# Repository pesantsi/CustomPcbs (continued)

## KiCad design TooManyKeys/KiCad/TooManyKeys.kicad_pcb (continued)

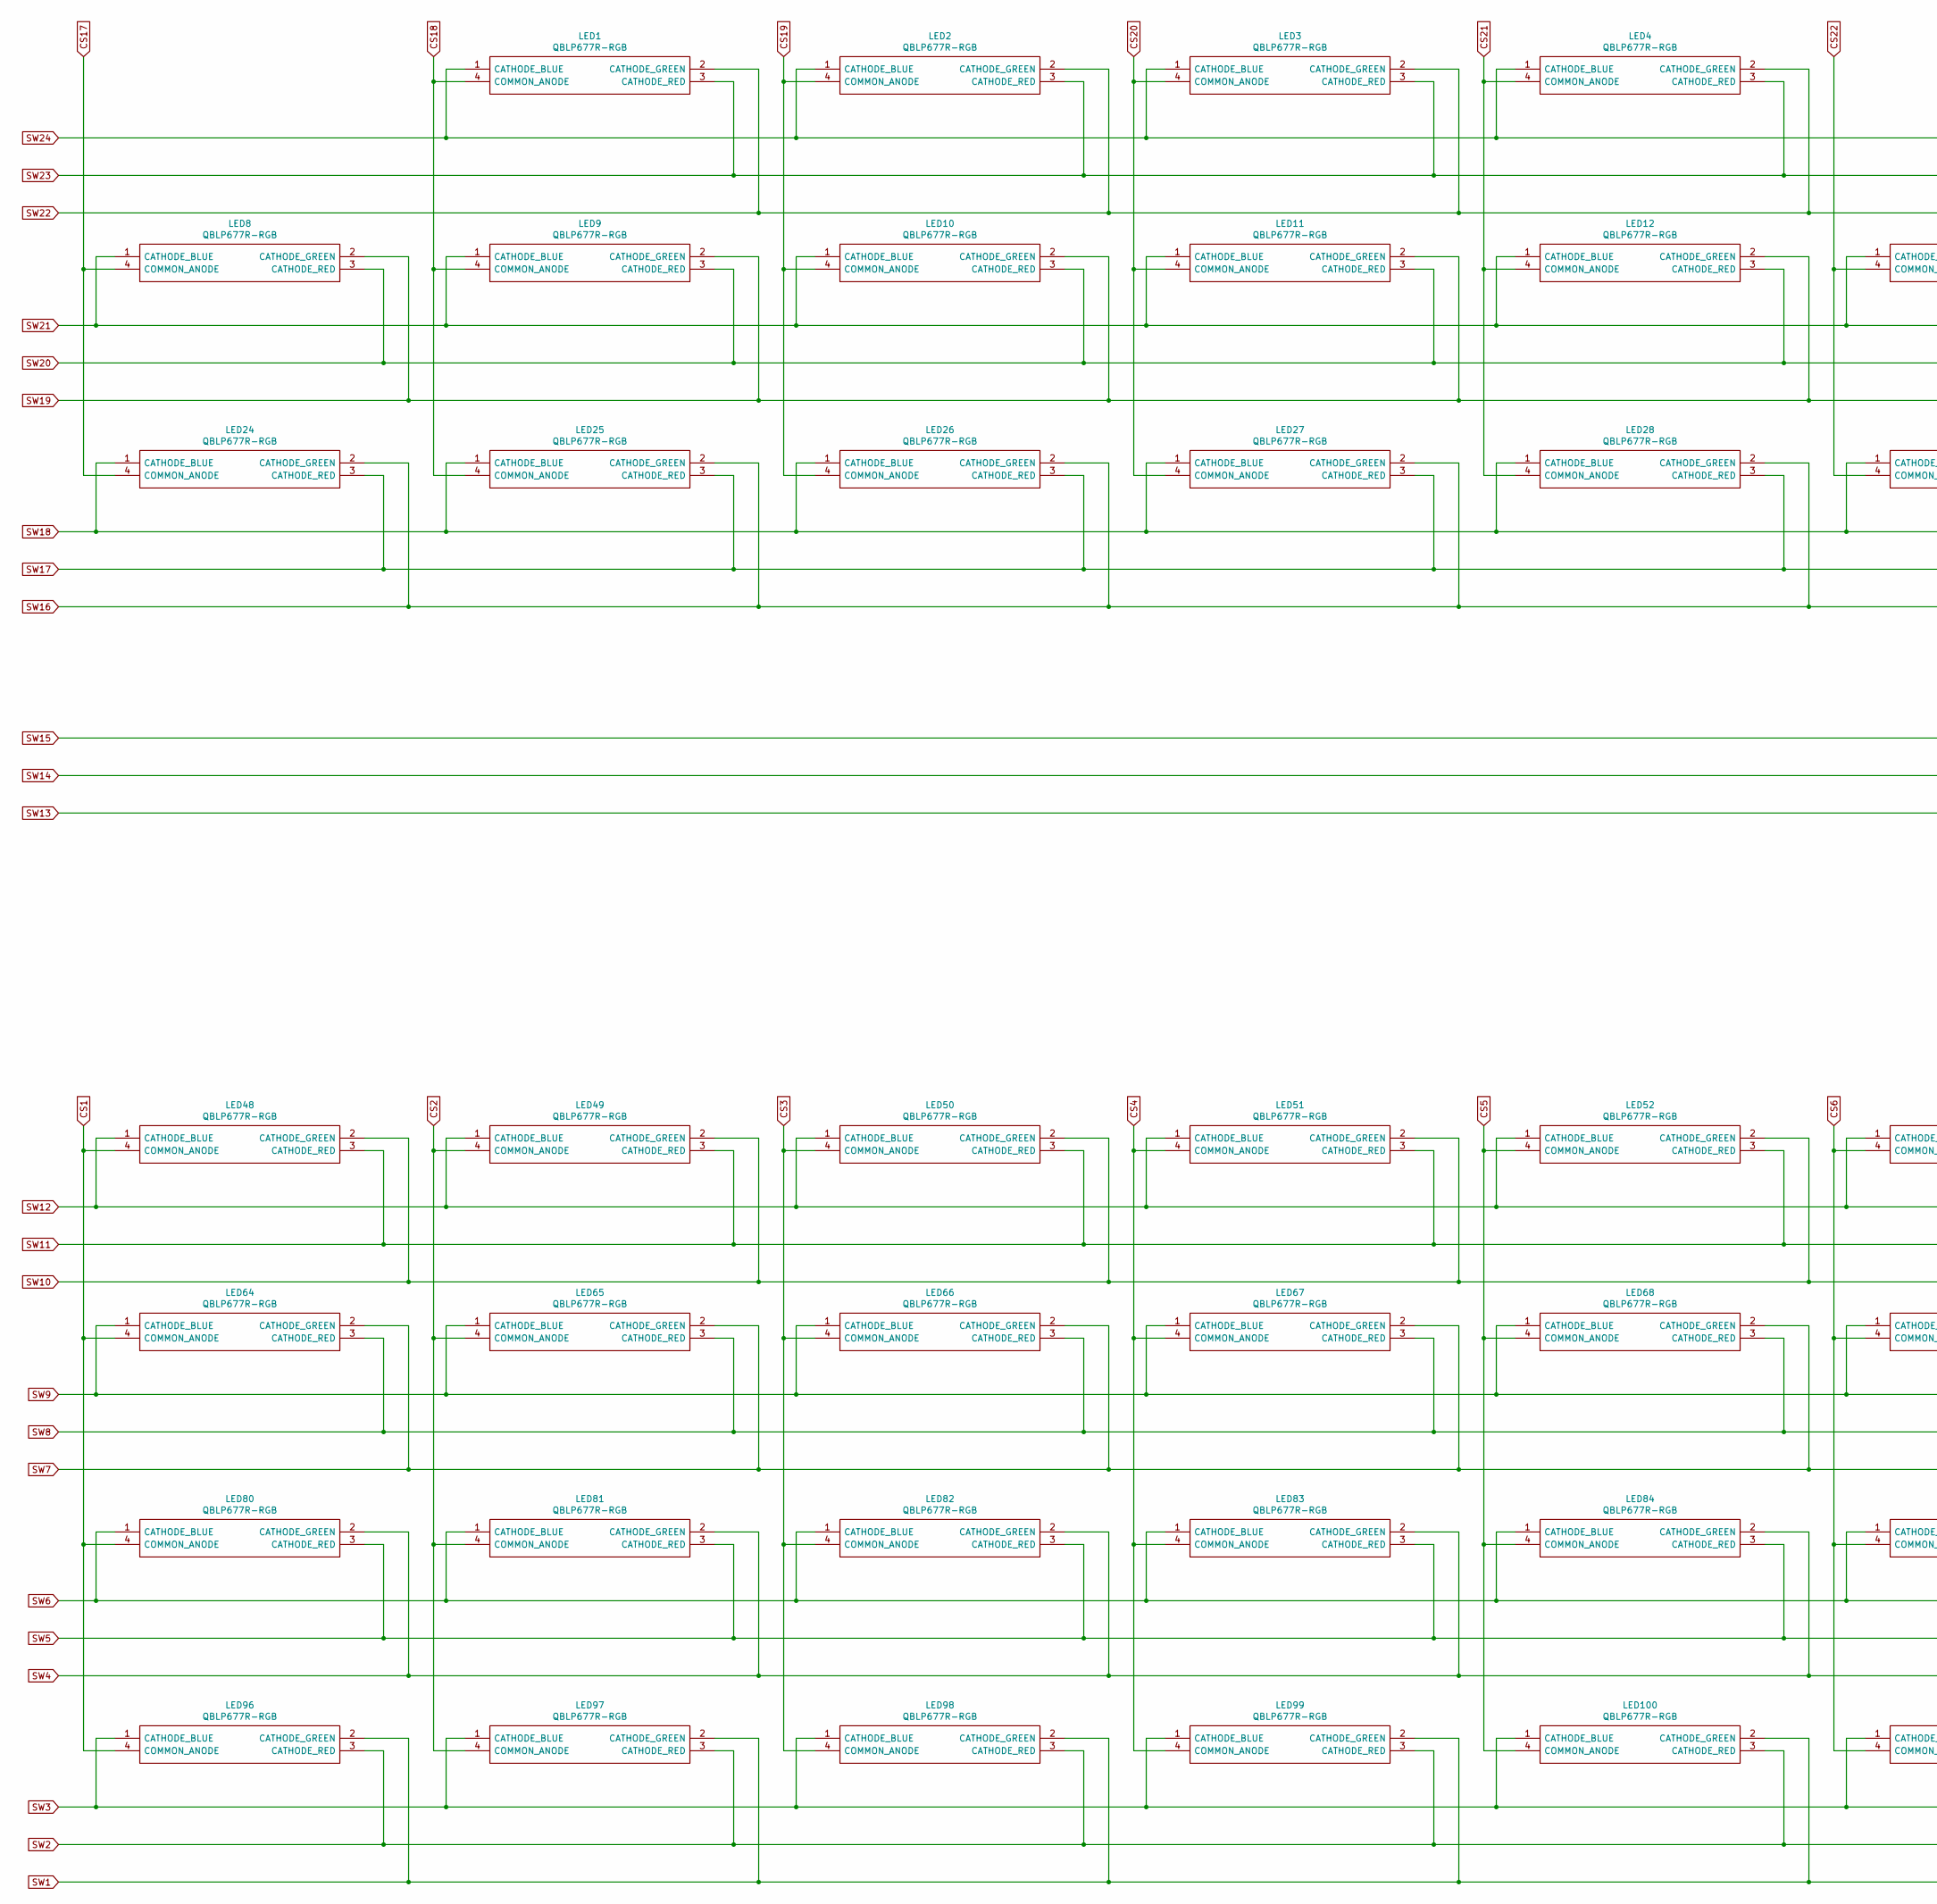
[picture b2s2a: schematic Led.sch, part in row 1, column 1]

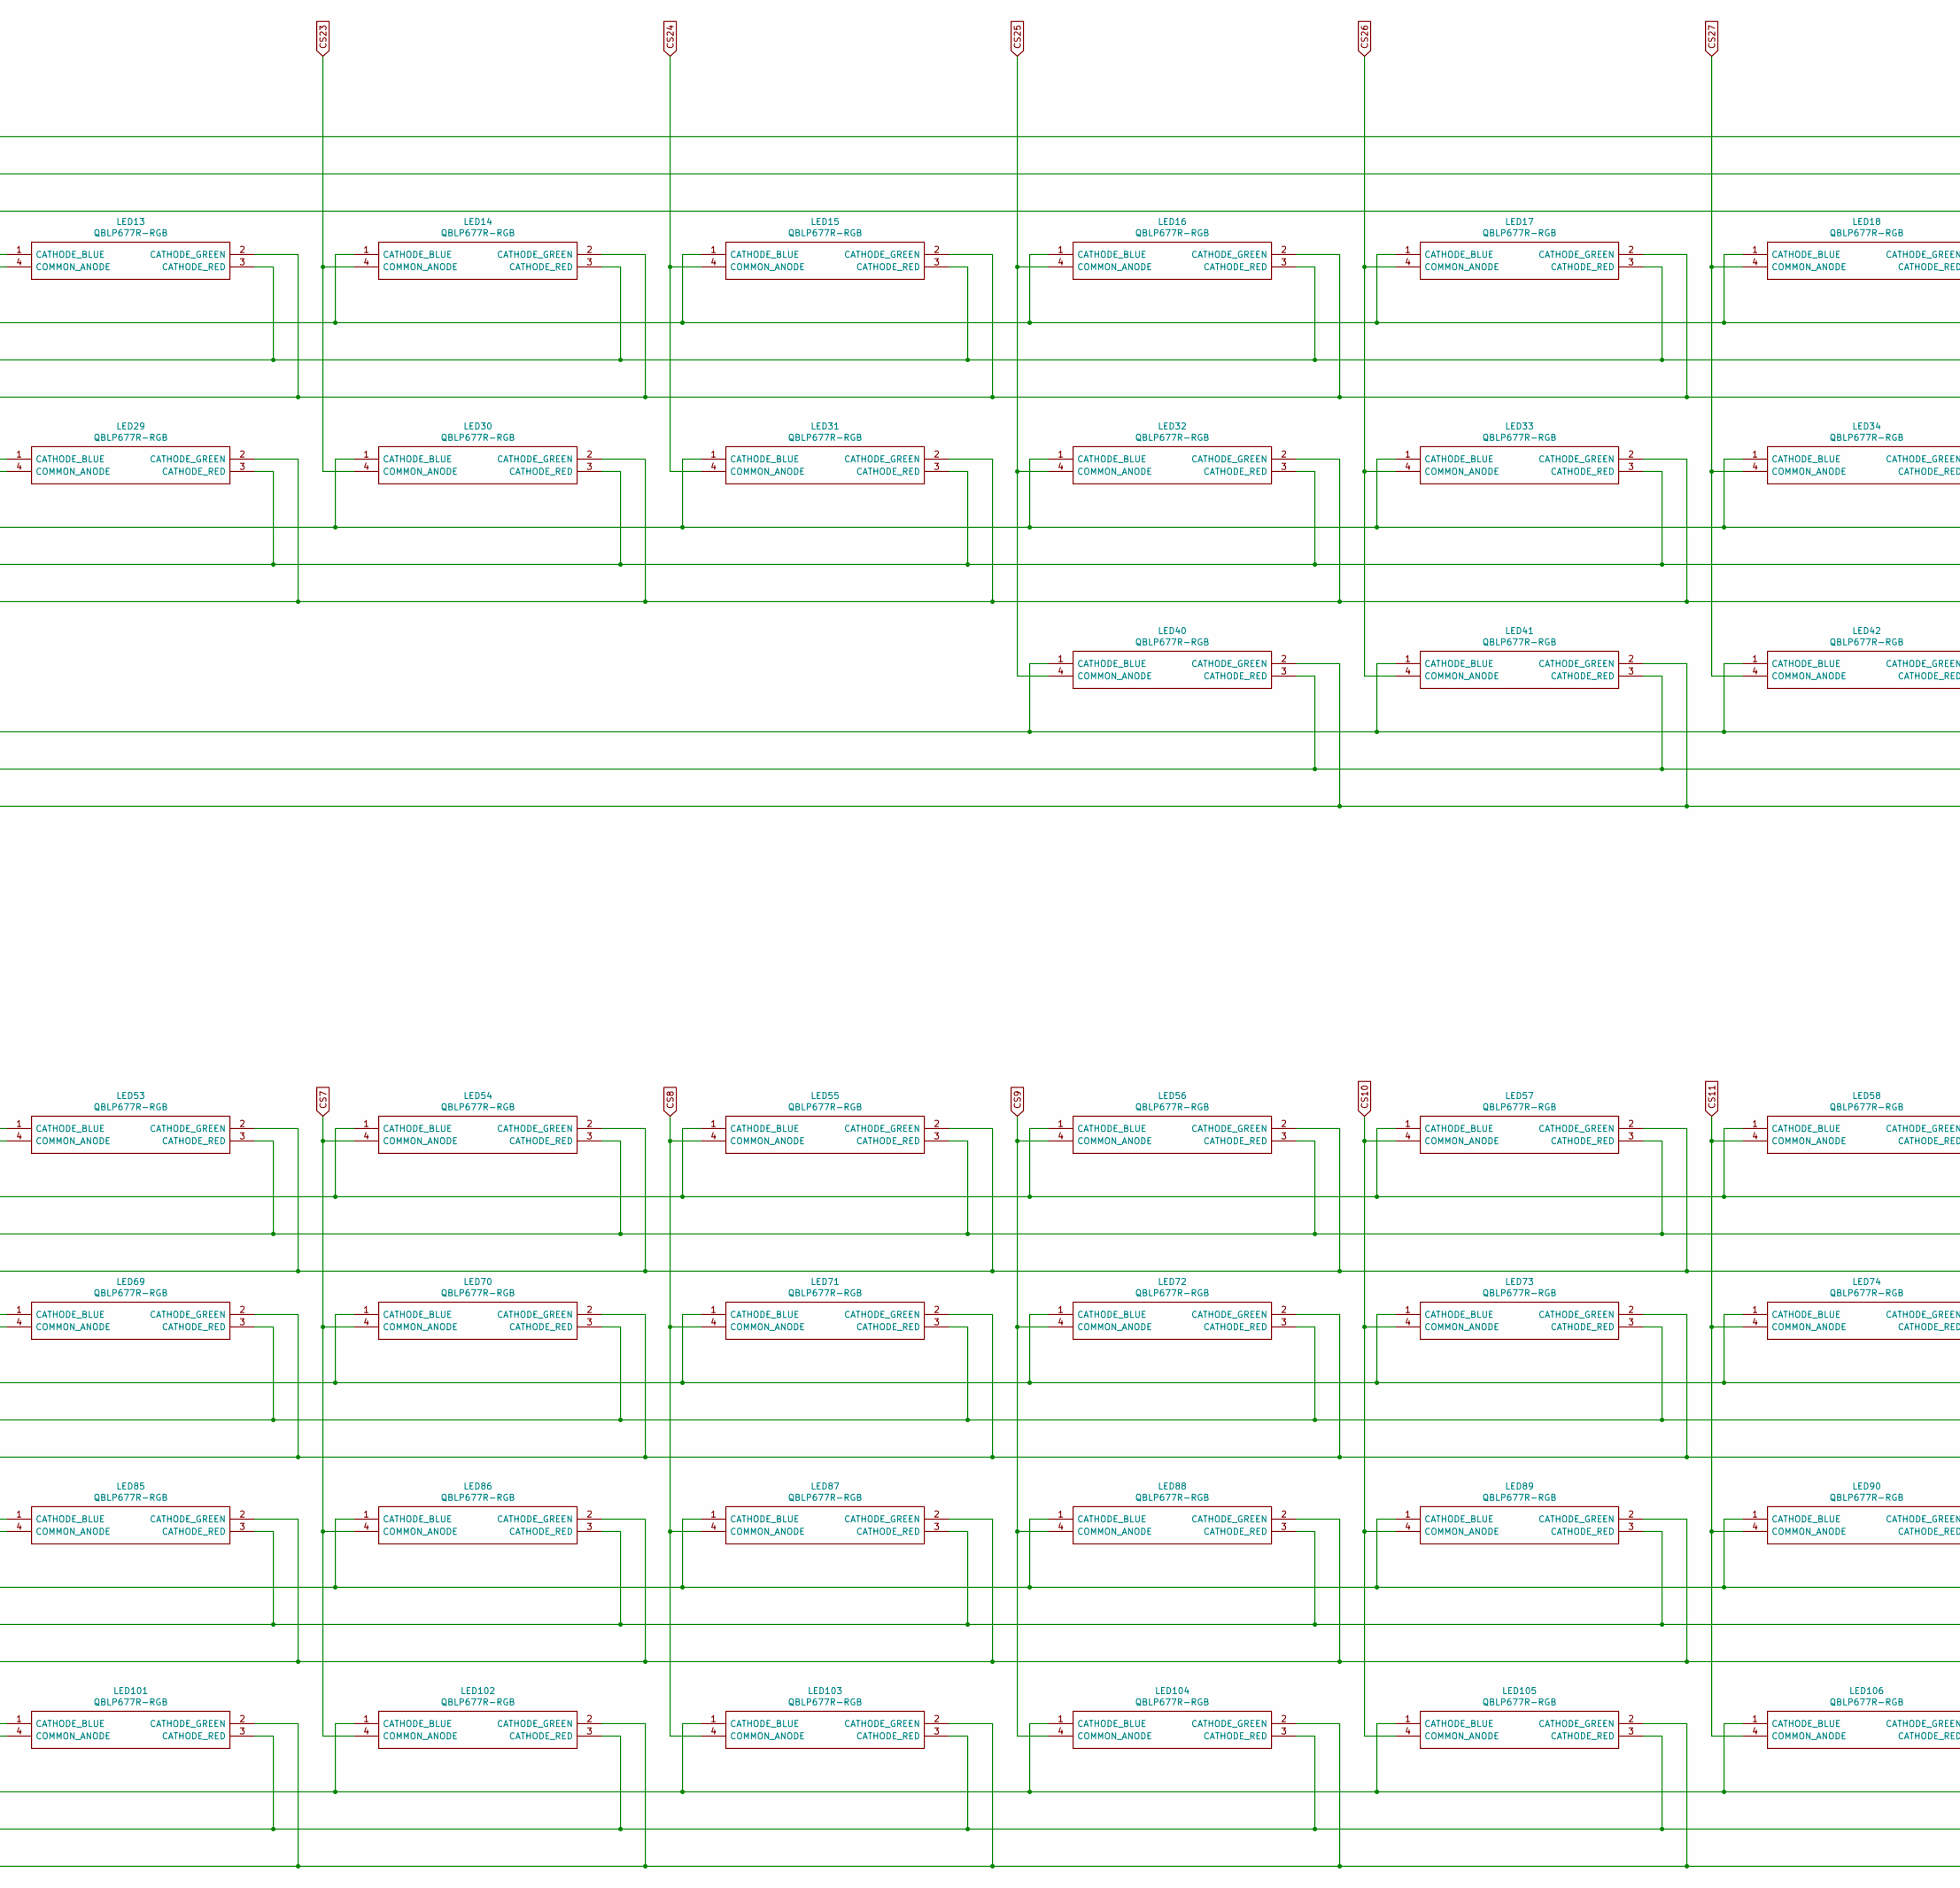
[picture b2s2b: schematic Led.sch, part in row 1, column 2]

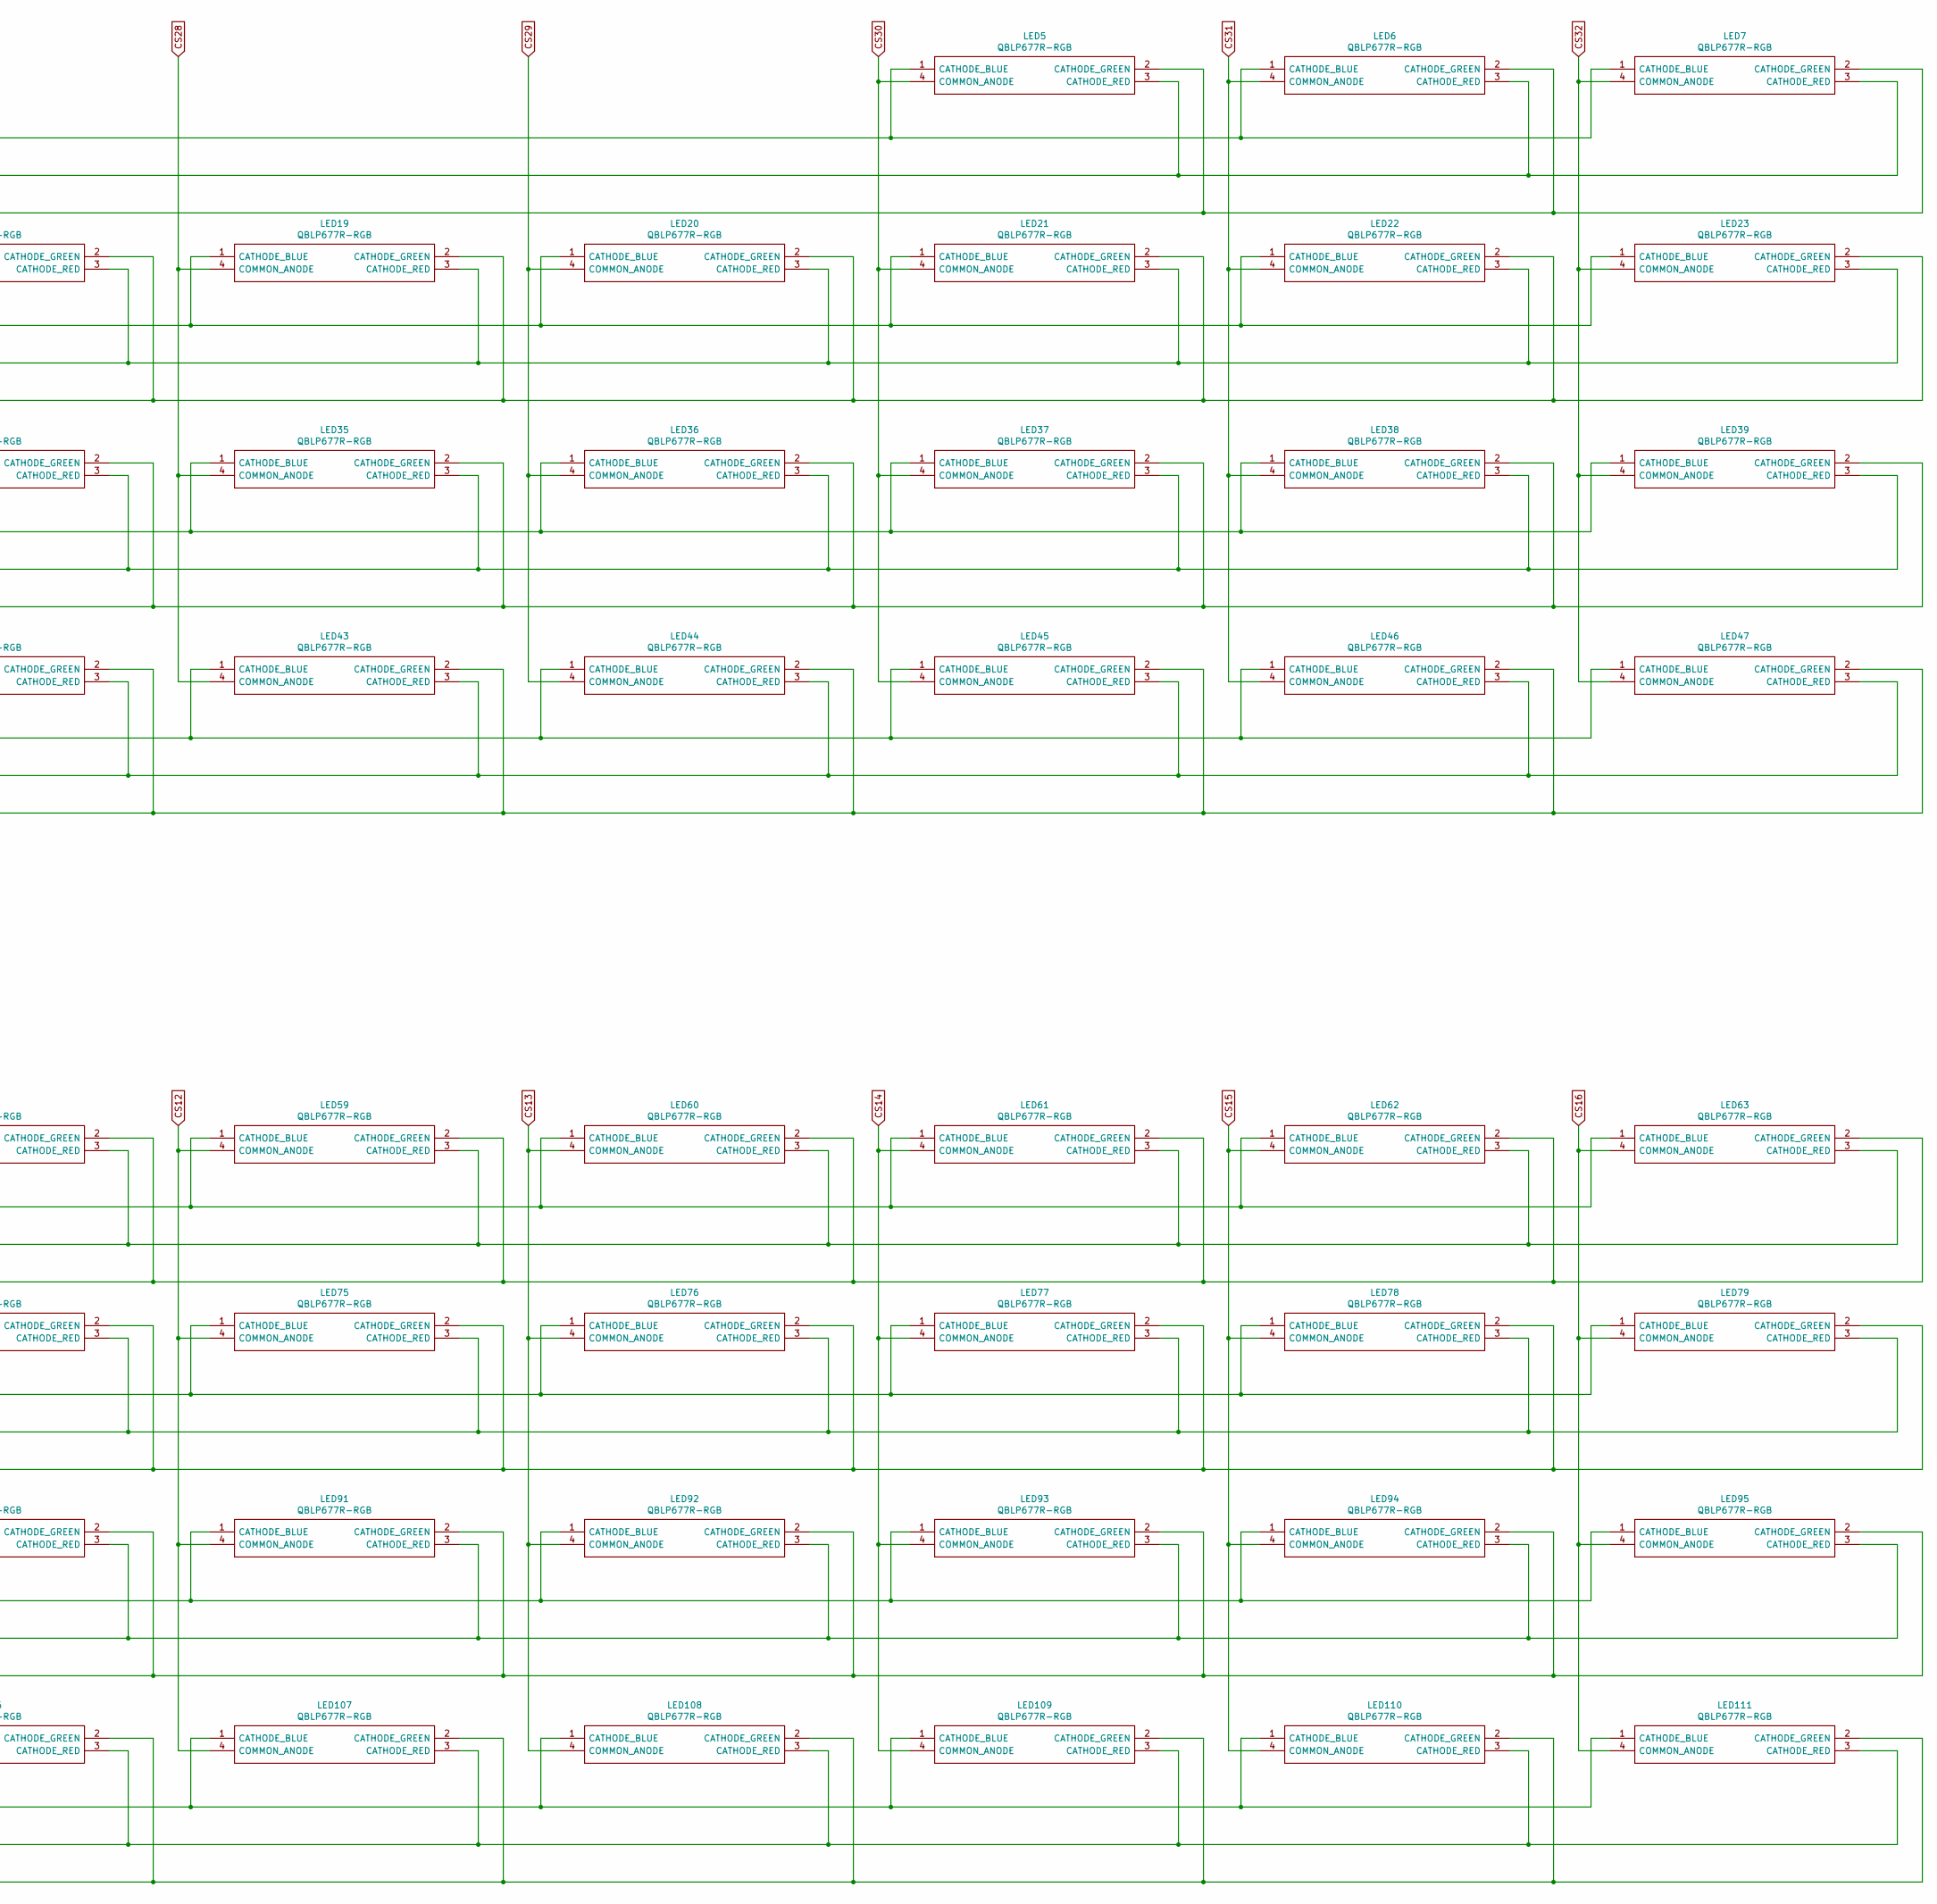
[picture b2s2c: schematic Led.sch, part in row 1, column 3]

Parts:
LED1, LED2, LED3, LED4, LED5, LED6, LED7, LED8, LED9, LED10, LED11, LED12, LED13, LED14, LED15, LED16, LED17, LED18, LED19, LED20, LED21, LED22, LED23, LED24, LED25, LED26, LED27, LED28, LED29, LED30, LED31, LED32, LED33, LED34, LED35, LED36, LED37, LED38, LED39, LED40, LED41, LED42, LED43, LED44, LED45, LED46, LED47, LED48, LED49, LED50, LED51, LED52, LED53, LED54, LED55, LED56, LED57, LED58, LED59, LED60, LED61, LED62, LED63, LED64, LED65, LED66, LED67, LED68, LED69, LED70, LED71, LED72, LED73, LED74, LED75, LED76, LED77, LED78, LED79, LED80, LED81, LED82, LED83, LED84, LED85, LED86, LED87, LED88, LED89, LED90, LED91, LED92, LED93, LED94, LED95, LED96, LED97, LED98, LED99, LED100, LED101, LED102, LED103, LED104, LED105, LED106, LED107, LED108, LED109, LED110, LED111: QBLP677R-RGB; Manufacturer_Part_Number QBLP677R-RGB

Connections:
CS1: LED48.4 (COMMON_ANODE), LED64.4 (COMMON_ANODE), LED80.4 (COMMON_ANODE), LED96.4 (COMMON_ANODE); also elsewhere on the board
CS2: LED49.4 (COMMON_ANODE), LED65.4 (COMMON_ANODE), LED81.4 (COMMON_ANODE), LED97.4 (COMMON_ANODE); also elsewhere on the board
CS3: LED50.4 (COMMON_ANODE), LED66.4 (COMMON_ANODE), LED82.4 (COMMON_ANODE), LED98.4 (COMMON_ANODE); also elsewhere on the board
CS4: LED51.4 (COMMON_ANODE), LED67.4 (COMMON_ANODE), LED83.4 (COMMON_ANODE), LED99.4 (COMMON_ANODE); also elsewhere on the board
CS5: LED52.4 (COMMON_ANODE), LED68.4 (COMMON_ANODE), LED84.4 (COMMON_ANODE), LED100.4 (COMMON_ANODE); also elsewhere on the board
CS6: LED53.4 (COMMON_ANODE), LED69.4 (COMMON_ANODE), LED85.4 (COMMON_ANODE), LED101.4 (COMMON_ANODE); also elsewhere on the board
CS7: LED54.4 (COMMON_ANODE), LED70.4 (COMMON_ANODE), LED86.4 (COMMON_ANODE), LED102.4 (COMMON_ANODE); also elsewhere on the board
CS8: LED55.4 (COMMON_ANODE), LED71.4 (COMMON_ANODE), LED87.4 (COMMON_ANODE), LED103.4 (COMMON_ANODE); also elsewhere on the board
CS9: LED56.4 (COMMON_ANODE), LED72.4 (COMMON_ANODE), LED88.4 (COMMON_ANODE), LED104.4 (COMMON_ANODE); also elsewhere on the board
CS10: LED57.4 (COMMON_ANODE), LED73.4 (COMMON_ANODE), LED89.4 (COMMON_ANODE), LED105.4 (COMMON_ANODE); also elsewhere on the board
CS11: LED58.4 (COMMON_ANODE), LED74.4 (COMMON_ANODE), LED90.4 (COMMON_ANODE), LED106.4 (COMMON_ANODE); also elsewhere on the board
CS12: LED59.4 (COMMON_ANODE), LED75.4 (COMMON_ANODE), LED91.4 (COMMON_ANODE), LED107.4 (COMMON_ANODE); also elsewhere on the board
CS13: LED60.4 (COMMON_ANODE), LED76.4 (COMMON_ANODE), LED92.4 (COMMON_ANODE), LED108.4 (COMMON_ANODE); also elsewhere on the board
CS14: LED61.4 (COMMON_ANODE), LED77.4 (COMMON_ANODE), LED93.4 (COMMON_ANODE), LED109.4 (COMMON_ANODE); also elsewhere on the board
CS15: LED62.4 (COMMON_ANODE), LED78.4 (COMMON_ANODE), LED94.4 (COMMON_ANODE), LED110.4 (COMMON_ANODE); also elsewhere on the board
CS16: LED63.4 (COMMON_ANODE), LED79.4 (COMMON_ANODE), LED95.4 (COMMON_ANODE), LED111.4 (COMMON_ANODE); also elsewhere on the board
CS17: LED8.4 (COMMON_ANODE), LED24.4 (COMMON_ANODE); also elsewhere on the board
CS18: LED1.4 (COMMON_ANODE), LED9.4 (COMMON_ANODE), LED25.4 (COMMON_ANODE); also elsewhere on the board
CS19: LED2.4 (COMMON_ANODE), LED10.4 (COMMON_ANODE), LED26.4 (COMMON_ANODE); also elsewhere on the board
CS20: LED3.4 (COMMON_ANODE), LED11.4 (COMMON_ANODE), LED27.4 (COMMON_ANODE); also elsewhere on the board
CS21: LED4.4 (COMMON_ANODE), LED12.4 (COMMON_ANODE), LED28.4 (COMMON_ANODE); also elsewhere on the board
CS22: LED13.4 (COMMON_ANODE), LED29.4 (COMMON_ANODE); also elsewhere on the board
CS23: LED14.4 (COMMON_ANODE), LED30.4 (COMMON_ANODE); also elsewhere on the board
CS24: LED15.4 (COMMON_ANODE), LED31.4 (COMMON_ANODE); also elsewhere on the board
CS25: LED16.4 (COMMON_ANODE), LED32.4 (COMMON_ANODE), LED40.4 (COMMON_ANODE); also elsewhere on the board
CS26: LED17.4 (COMMON_ANODE), LED33.4 (COMMON_ANODE), LED41.4 (COMMON_ANODE); also elsewhere on the board
CS27: LED18.4 (COMMON_ANODE), LED34.4 (COMMON_ANODE), LED42.4 (COMMON_ANODE); also elsewhere on the board
CS28: LED19.4 (COMMON_ANODE), LED35.4 (COMMON_ANODE), LED43.4 (COMMON_ANODE); also elsewhere on the board
CS29: LED20.4 (COMMON_ANODE), LED36.4 (COMMON_ANODE), LED44.4 (COMMON_ANODE); also elsewhere on the board
CS30: LED5.4 (COMMON_ANODE), LED21.4 (COMMON_ANODE), LED37.4 (COMMON_ANODE), LED45.4 (COMMON_ANODE); also elsewhere on the board
CS31: LED6.4 (COMMON_ANODE), LED22.4 (COMMON_ANODE), LED38.4 (COMMON_ANODE), LED46.4 (COMMON_ANODE); also elsewhere on the board
CS32: LED7.4 (COMMON_ANODE), LED23.4 (COMMON_ANODE), LED39.4 (COMMON_ANODE), LED47.4 (COMMON_ANODE); also elsewhere on the board
SW1: LED96.2 (CATHODE_GREEN), LED97.2 (CATHODE_GREEN), LED98.2 (CATHODE_GREEN), LED99.2 (CATHODE_GREEN), LED100.2 (CATHODE_GREEN), LED101.2 (CATHODE_GREEN), LED102.2 (CATHODE_GREEN), LED103.2 (CATHODE_GREEN), LED104.2 (CATHODE_GREEN), LED105.2 (CATHODE_GREEN), LED106.2 (CATHODE_GREEN), LED107.2 (CATHODE_GREEN), LED108.2 (CATHODE_GREEN), LED109.2 (CATHODE_GREEN), LED110.2 (CATHODE_GREEN), LED111.2 (CATHODE_GREEN); also elsewhere on the board
SW2: LED96.3 (CATHODE_RED), LED97.3 (CATHODE_RED), LED98.3 (CATHODE_RED), LED99.3 (CATHODE_RED), LED100.3 (CATHODE_RED), LED101.3 (CATHODE_RED), LED102.3 (CATHODE_RED), LED103.3 (CATHODE_RED), LED104.3 (CATHODE_RED), LED105.3 (CATHODE_RED), LED106.3 (CATHODE_RED), LED107.3 (CATHODE_RED), LED108.3 (CATHODE_RED), LED109.3 (CATHODE_RED), LED110.3 (CATHODE_RED), LED111.3 (CATHODE_RED); also elsewhere on the board
SW3: LED96.1 (CATHODE_BLUE), LED97.1 (CATHODE_BLUE), LED98.1 (CATHODE_BLUE), LED99.1 (CATHODE_BLUE), LED100.1 (CATHODE_BLUE), LED101.1 (CATHODE_BLUE), LED102.1 (CATHODE_BLUE), LED103.1 (CATHODE_BLUE), LED104.1 (CATHODE_BLUE), LED105.1 (CATHODE_BLUE), LED106.1 (CATHODE_BLUE), LED107.1 (CATHODE_BLUE), LED108.1 (CATHODE_BLUE), LED109.1 (CATHODE_BLUE), LED110.1 (CATHODE_BLUE), LED111.1 (CATHODE_BLUE); also elsewhere on the board
SW4: LED80.2 (CATHODE_GREEN), LED81.2 (CATHODE_GREEN), LED82.2 (CATHODE_GREEN), LED83.2 (CATHODE_GREEN), LED84.2 (CATHODE_GREEN), LED85.2 (CATHODE_GREEN), LED86.2 (CATHODE_GREEN), LED87.2 (CATHODE_GREEN), LED88.2 (CATHODE_GREEN), LED89.2 (CATHODE_GREEN), LED90.2 (CATHODE_GREEN), LED91.2 (CATHODE_GREEN), LED92.2 (CATHODE_GREEN), LED93.2 (CATHODE_GREEN), LED94.2 (CATHODE_GREEN), LED95.2 (CATHODE_GREEN); also elsewhere on the board
SW5: LED80.3 (CATHODE_RED), LED81.3 (CATHODE_RED), LED82.3 (CATHODE_RED), LED83.3 (CATHODE_RED), LED84.3 (CATHODE_RED), LED85.3 (CATHODE_RED), LED86.3 (CATHODE_RED), LED87.3 (CATHODE_RED), LED88.3 (CATHODE_RED), LED89.3 (CATHODE_RED), LED90.3 (CATHODE_RED), LED91.3 (CATHODE_RED), LED92.3 (CATHODE_RED), LED93.3 (CATHODE_RED), LED94.3 (CATHODE_RED), LED95.3 (CATHODE_RED); also elsewhere on the board
SW6: LED80.1 (CATHODE_BLUE), LED81.1 (CATHODE_BLUE), LED82.1 (CATHODE_BLUE), LED83.1 (CATHODE_BLUE), LED84.1 (CATHODE_BLUE), LED85.1 (CATHODE_BLUE), LED86.1 (CATHODE_BLUE), LED87.1 (CATHODE_BLUE), LED88.1 (CATHODE_BLUE), LED89.1 (CATHODE_BLUE), LED90.1 (CATHODE_BLUE), LED91.1 (CATHODE_BLUE), LED92.1 (CATHODE_BLUE), LED93.1 (CATHODE_BLUE), LED94.1 (CATHODE_BLUE), LED95.1 (CATHODE_BLUE); also elsewhere on the board
SW7: LED64.2 (CATHODE_GREEN), LED65.2 (CATHODE_GREEN), LED66.2 (CATHODE_GREEN), LED67.2 (CATHODE_GREEN), LED68.2 (CATHODE_GREEN), LED69.2 (CATHODE_GREEN), LED70.2 (CATHODE_GREEN), LED71.2 (CATHODE_GREEN), LED72.2 (CATHODE_GREEN), LED73.2 (CATHODE_GREEN), LED74.2 (CATHODE_GREEN), LED75.2 (CATHODE_GREEN), LED76.2 (CATHODE_GREEN), LED77.2 (CATHODE_GREEN), LED78.2 (CATHODE_GREEN), LED79.2 (CATHODE_GREEN); also elsewhere on the board
SW8: LED64.3 (CATHODE_RED), LED65.3 (CATHODE_RED), LED66.3 (CATHODE_RED), LED67.3 (CATHODE_RED), LED68.3 (CATHODE_RED), LED69.3 (CATHODE_RED), LED70.3 (CATHODE_RED), LED71.3 (CATHODE_RED), LED72.3 (CATHODE_RED), LED73.3 (CATHODE_RED), LED74.3 (CATHODE_RED), LED75.3 (CATHODE_RED), LED76.3 (CATHODE_RED), LED77.3 (CATHODE_RED), LED78.3 (CATHODE_RED), LED79.3 (CATHODE_RED); also elsewhere on the board
SW9: LED64.1 (CATHODE_BLUE), LED65.1 (CATHODE_BLUE), LED66.1 (CATHODE_BLUE), LED67.1 (CATHODE_BLUE), LED68.1 (CATHODE_BLUE), LED69.1 (CATHODE_BLUE), LED70.1 (CATHODE_BLUE), LED71.1 (CATHODE_BLUE), LED72.1 (CATHODE_BLUE), LED73.1 (CATHODE_BLUE), LED74.1 (CATHODE_BLUE), LED75.1 (CATHODE_BLUE), LED76.1 (CATHODE_BLUE), LED77.1 (CATHODE_BLUE), LED78.1 (CATHODE_BLUE), LED79.1 (CATHODE_BLUE); also elsewhere on the board
SW10: LED48.2 (CATHODE_GREEN), LED49.2 (CATHODE_GREEN), LED50.2 (CATHODE_GREEN), LED51.2 (CATHODE_GREEN), LED52.2 (CATHODE_GREEN), LED53.2 (CATHODE_GREEN), LED54.2 (CATHODE_GREEN), LED55.2 (CATHODE_GREEN), LED56.2 (CATHODE_GREEN), LED57.2 (CATHODE_GREEN), LED58.2 (CATHODE_GREEN), LED59.2 (CATHODE_GREEN), LED60.2 (CATHODE_GREEN), LED61.2 (CATHODE_GREEN), LED62.2 (CATHODE_GREEN), LED63.2 (CATHODE_GREEN); also elsewhere on the board
SW11: LED48.3 (CATHODE_RED), LED49.3 (CATHODE_RED), LED50.3 (CATHODE_RED), LED51.3 (CATHODE_RED), LED52.3 (CATHODE_RED), LED53.3 (CATHODE_RED), LED54.3 (CATHODE_RED), LED55.3 (CATHODE_RED), LED56.3 (CATHODE_RED), LED57.3 (CATHODE_RED), LED58.3 (CATHODE_RED), LED59.3 (CATHODE_RED), LED60.3 (CATHODE_RED), LED61.3 (CATHODE_RED), LED62.3 (CATHODE_RED), LED63.3 (CATHODE_RED); also elsewhere on the board
SW12: LED48.1 (CATHODE_BLUE), LED49.1 (CATHODE_BLUE), LED50.1 (CATHODE_BLUE), LED51.1 (CATHODE_BLUE), LED52.1 (CATHODE_BLUE), LED53.1 (CATHODE_BLUE), LED54.1 (CATHODE_BLUE), LED55.1 (CATHODE_BLUE), LED56.1 (CATHODE_BLUE), LED57.1 (CATHODE_BLUE), LED58.1 (CATHODE_BLUE), LED59.1 (CATHODE_BLUE), LED60.1 (CATHODE_BLUE), LED61.1 (CATHODE_BLUE), LED62.1 (CATHODE_BLUE), LED63.1 (CATHODE_BLUE); also elsewhere on the board
SW13: LED40.2 (CATHODE_GREEN), LED41.2 (CATHODE_GREEN), LED42.2 (CATHODE_GREEN), LED43.2 (CATHODE_GREEN), LED44.2 (CATHODE_GREEN), LED45.2 (CATHODE_GREEN), LED46.2 (CATHODE_GREEN), LED47.2 (CATHODE_GREEN); also elsewhere on the board
SW14: LED40.3 (CATHODE_RED), LED41.3 (CATHODE_RED), LED42.3 (CATHODE_RED), LED43.3 (CATHODE_RED), LED44.3 (CATHODE_RED), LED45.3 (CATHODE_RED), LED46.3 (CATHODE_RED), LED47.3 (CATHODE_RED); also elsewhere on the board
SW15: LED40.1 (CATHODE_BLUE), LED41.1 (CATHODE_BLUE), LED42.1 (CATHODE_BLUE), LED43.1 (CATHODE_BLUE), LED44.1 (CATHODE_BLUE), LED45.1 (CATHODE_BLUE), LED46.1 (CATHODE_BLUE), LED47.1 (CATHODE_BLUE); also elsewhere on the board
SW16: LED24.2 (CATHODE_GREEN), LED25.2 (CATHODE_GREEN), LED26.2 (CATHODE_GREEN), LED27.2 (CATHODE_GREEN), LED28.2 (CATHODE_GREEN), LED29.2 (CATHODE_GREEN), LED30.2 (CATHODE_GREEN), LED31.2 (CATHODE_GREEN), LED32.2 (CATHODE_GREEN), LED33.2 (CATHODE_GREEN), LED34.2 (CATHODE_GREEN), LED35.2 (CATHODE_GREEN), LED36.2 (CATHODE_GREEN), LED37.2 (CATHODE_GREEN), LED38.2 (CATHODE_GREEN), LED39.2 (CATHODE_GREEN); also elsewhere on the board
SW17: LED24.3 (CATHODE_RED), LED25.3 (CATHODE_RED), LED26.3 (CATHODE_RED), LED27.3 (CATHODE_RED), LED28.3 (CATHODE_RED), LED29.3 (CATHODE_RED), LED30.3 (CATHODE_RED), LED31.3 (CATHODE_RED), LED32.3 (CATHODE_RED), LED33.3 (CATHODE_RED), LED34.3 (CATHODE_RED), LED35.3 (CATHODE_RED), LED36.3 (CATHODE_RED), LED37.3 (CATHODE_RED), LED38.3 (CATHODE_RED), LED39.3 (CATHODE_RED); also elsewhere on the board
SW18: LED24.1 (CATHODE_BLUE), LED25.1 (CATHODE_BLUE), LED26.1 (CATHODE_BLUE), LED27.1 (CATHODE_BLUE), LED28.1 (CATHODE_BLUE), LED29.1 (CATHODE_BLUE), LED30.1 (CATHODE_BLUE), LED31.1 (CATHODE_BLUE), LED32.1 (CATHODE_BLUE), LED33.1 (CATHODE_BLUE), LED34.1 (CATHODE_BLUE), LED35.1 (CATHODE_BLUE), LED36.1 (CATHODE_BLUE), LED37.1 (CATHODE_BLUE), LED38.1 (CATHODE_BLUE), LED39.1 (CATHODE_BLUE); also elsewhere on the board
SW19: LED8.2 (CATHODE_GREEN), LED9.2 (CATHODE_GREEN), LED10.2 (CATHODE_GREEN), LED11.2 (CATHODE_GREEN), LED12.2 (CATHODE_GREEN), LED13.2 (CATHODE_GREEN), LED14.2 (CATHODE_GREEN), LED15.2 (CATHODE_GREEN), LED16.2 (CATHODE_GREEN), LED17.2 (CATHODE_GREEN), LED18.2 (CATHODE_GREEN), LED19.2 (CATHODE_GREEN), LED20.2 (CATHODE_GREEN), LED21.2 (CATHODE_GREEN), LED22.2 (CATHODE_GREEN), LED23.2 (CATHODE_GREEN); also elsewhere on the board
SW20: LED8.3 (CATHODE_RED), LED9.3 (CATHODE_RED), LED10.3 (CATHODE_RED), LED11.3 (CATHODE_RED), LED12.3 (CATHODE_RED), LED13.3 (CATHODE_RED), LED14.3 (CATHODE_RED), LED15.3 (CATHODE_RED), LED16.3 (CATHODE_RED), LED17.3 (CATHODE_RED), LED18.3 (CATHODE_RED), LED19.3 (CATHODE_RED), LED20.3 (CATHODE_RED), LED21.3 (CATHODE_RED), LED22.3 (CATHODE_RED), LED23.3 (CATHODE_RED); also elsewhere on the board
SW21: LED8.1 (CATHODE_BLUE), LED9.1 (CATHODE_BLUE), LED10.1 (CATHODE_BLUE), LED11.1 (CATHODE_BLUE), LED12.1 (CATHODE_BLUE), LED13.1 (CATHODE_BLUE), LED14.1 (CATHODE_BLUE), LED15.1 (CATHODE_BLUE), LED16.1 (CATHODE_BLUE), LED17.1 (CATHODE_BLUE), LED18.1 (CATHODE_BLUE), LED19.1 (CATHODE_BLUE), LED20.1 (CATHODE_BLUE), LED21.1 (CATHODE_BLUE), LED22.1 (CATHODE_BLUE), LED23.1 (CATHODE_BLUE); also elsewhere on the board
SW22: LED1.2 (CATHODE_GREEN), LED2.2 (CATHODE_GREEN), LED3.2 (CATHODE_GREEN), LED4.2 (CATHODE_GREEN), LED5.2 (CATHODE_GREEN), LED6.2 (CATHODE_GREEN), LED7.2 (CATHODE_GREEN); also elsewhere on the board
SW23: LED1.3 (CATHODE_RED), LED2.3 (CATHODE_RED), LED3.3 (CATHODE_RED), LED4.3 (CATHODE_RED), LED5.3 (CATHODE_RED), LED6.3 (CATHODE_RED), LED7.3 (CATHODE_RED); also elsewhere on the board
SW24: LED1.1 (CATHODE_BLUE), LED2.1 (CATHODE_BLUE), LED3.1 (CATHODE_BLUE), LED4.1 (CATHODE_BLUE), LED5.1 (CATHODE_BLUE), LED6.1 (CATHODE_BLUE), LED7.1 (CATHODE_BLUE); also elsewhere on the board
